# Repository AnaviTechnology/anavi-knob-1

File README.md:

# ANAVI Knob 1

**Open source mini programmable keypad with a rotary encoder**

ANAVI Knob 1 is a mini mechanical keyboard with a clickable rotary encoder, USB-C and Raspberry Pi RP2040 microcontroller. It is a tiny input device with a single rotary encoder with a clickable switch and a RGB LED. You can turn it left, you can turn it right, and you can click it. It is fully programmable and there is an I²C slot you can use to add peripherals, for example a mini OLED display.

ANAVI Knob 1 has been designed with [the cross platform and open source electronics design automation suite KiCad](https://kicad.org/).

[ANAVI Knob 1, ANAVI Knobs 3 and ANAVI Macro Pad 10 were brought to market through a crowdfunding campaign at Crowd Supply](https://www.crowdsupply.com/anavi-technology/anavi-macro-pad-10). For more details please visit https://anavi.technology/

# License

The project is released under the [Creative Commons Attribution-ShareAlike 4.0 International (CC BY-SA 4.0)](https://creativecommons.org/licenses/by-sa/4.0/).

Note: This is a human-readable summary of (and not a substitute for) the [license](https://creativecommons.org/licenses/by-sa/4.0/legalcode).

You are free to:

Share — copy and redistribute the material in any medium or format Adapt — remix, transform, and build upon the material for any purpose, even commercially. The licensor cannot revoke these freedoms as long as you follow the license terms. Under the following terms:

Attribution — You must give appropriate credit, provide a link to the license, and indicate if changes were made. You may do so in any reasonable manner, but not in any way that suggests the licensor endorses you or your use. ShareAlike — If you remix, transform, or build upon the material, you must distribute your contributions under the same license as the original. No additional restrictions — You may not apply legal terms or technological measures that legally restrict others from doing anything the license permits. Notices:

You do not have to comply with the license for elements of the material in the public domain or where your use is permitted by an applicable exception or limitation. No warranties are given. The license may not give you all of the permissions necessary for your intended use. For example, other rights such as publicity, privacy, or moral rights may limit how you use the material.

You will have to provide a link to the original creator of the project http://www.anavi.technology on any documentation or website.

Credit can be attributed through a link to the creator website: http://www.anavi.technology

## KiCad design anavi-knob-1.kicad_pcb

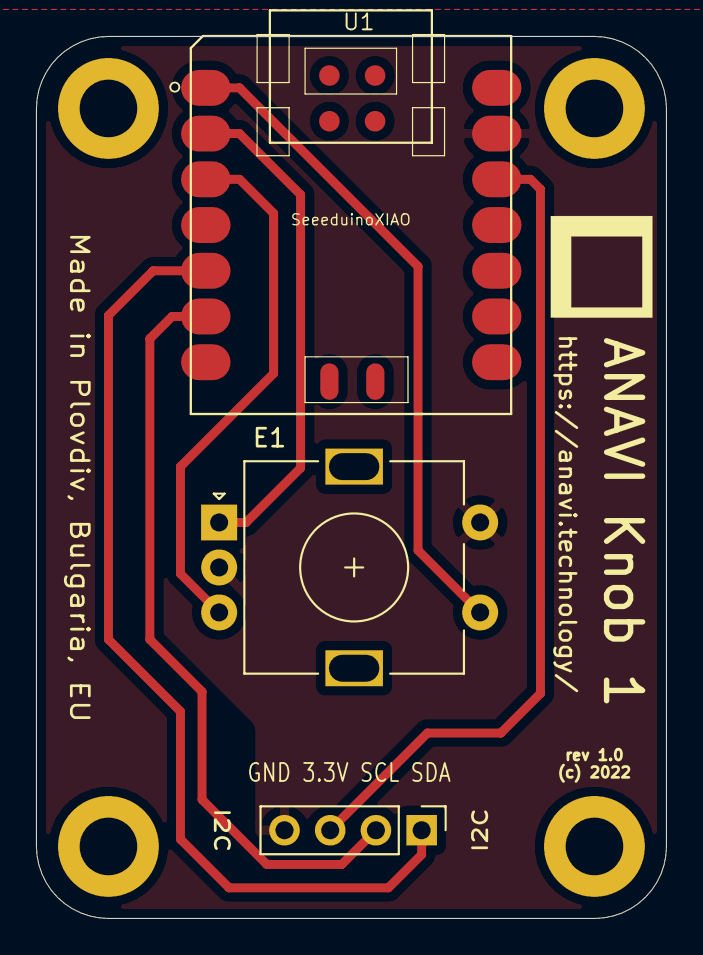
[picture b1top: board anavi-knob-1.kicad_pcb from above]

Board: 2 copper layers, 35.0 x 49.0 mm, 3 parts (0 on the bottom side), 7 nets.

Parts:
E1: Rotary_Encoder_Switch; RotaryEncoder_Alps_EC11E-Switch_Vertical_H20mm
I2C: Conn_01x04_Female; PinHeader_1x04_P2.54mm_Vertical
U1: SeeeduinoXIAO; Seeeduino XIAO-MOUDLE14P-2.54-21X17.8MM

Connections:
+3V3: I2C.3, U1.12
GND: E1.C, E1.S2, I2C.4, U1.13
unnamed: E1.A, U1.2
unnamed: E1.B, U1.3
unnamed: E1.S1, U1.1
unnamed: I2C.1, U1.5
unnamed: I2C.2, U1.6

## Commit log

2022-05-20 anavi-knob-1: Initial commit
    Initial commit of ANAVI Knob 1.
2022-06-28 anavi-knob-1.kicad_pcb: Draw enclosures
    Draw enclosure on the fabrication layer.
2022-10-31 README.md: Update description
    Update description about ANAVI Knob 1.
2022-10-31 README.md: Add images
    Add ANAVI Knob 1 images.
2024-02-06 README.md: Fix KiCad URL

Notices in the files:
anavi-knob-1.kicad_pcb:
(c) 2022
